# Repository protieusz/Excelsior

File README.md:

# Excelsior
Excelsior, 34 keys unisplit ortho with staggered pinkies &amp; 25mm trackball, optional RGB strip.

# Description
Excelsior is a heavily modified version of Endzone34 which has been blessed by takashicompany himself for the mod. [Endzone34](https://github.com/takashicompany/endzone34) was originally designed by takashicompany.

A List Of Mods Made To The Original PCB by [takashicompany](https://github.com/takashicompany/endzone34):

-PCB was created from scratch using the outline shape of Endzone34 using EasyEDA.

-A circular hole was created in the middle that can accomodate either a 25mm trackball powered by PMW3360 sensor.

-Base of the trackball holder with lens cut out is integrated into the top case with integrated 5mm switch plate. Top case sits flush with pcb.

-This PCB is capable of hot swap, Kailh.

-Full keyboard case was created to house the PCB.

-MCU area is now hidden and have an extrude of a [Starship logo](https://www.clipartmax.com/middle/m2i8Z5m2d3b1K9m2_star-trek-ship-icon-icon/)

-Excelsior is powered by [RP2040 Zero Raspberry Pi SuperMini Pico](https://www.aliexpress.com/item/1005007292787135.html?spm=a2g0o.order_list.order_list_main.136.6e251802pcq7qH) which you can get from AE and is soldered at the bottom of the pcb flush to the pcb.

-For diodes, I decided to try out the [BAV70](https://www.lcsc.com/product-detail/Switching-Diode_Jiangsu-Changjing-Electronics-Technology-Co-Ltd-BAV70_C68978.html) so that I solder less diodes since this pcb
is not sponsored. I would only need to solder on 17 diodes instead of 34.

-PCB has the option of RGB strip and the power 5v has the proper power level shifter component soldered on. Initially I was gonna do individual 34 RGBs but too much work and I don't use RGBs that often.

-QMK code is borrowed from aki27 bally and modified the matrix to fit my Excelsior. No suppport will be given since I just copy and paste.

-Keycaps I prefer high profile ones, MT3 or SA.

-Use M2 brass hot inserts 3.2mm diameter and 4mm length for the M2 screws to secure the case. I forgot how long is my M2 screws are but they should be greater than 10mm so estimated around 14.6mm. Play around with and buy multiple M2 lenght screws.

# Disclaimer
The trackball user experience might differ depending on the types of 3D printer that you use or if the printers were calibrated properly. It might be a hit and miss. The experience can also be adjust on the QMK side on the CPI settings. No
support will be given since the code was copy pasted from bally by aki27. As for the ball material and sizing plays a big role on the user experience. I personally prefer the BOM ball 25mm compared to the other different materials. Try it out and experiment it. As per usual print and use at your own risk. No support will be given. This design is MIT licensed so that means you can modify and do whatever you want with the design. If you do modify my design, please be kind to give me a shout out. PCB file is converted from EasyEDA so the convertion accuracy might not be good and KiCad DRC will scream but on EasyEDA DRC is fine. As the time of writing, the Excelsior is 100% working with no issues on my end.  Results might differ on your end.  A all in one Fusion file for the case that include the sketches is also included in this GitHub.  Thanks. 

# Full Production Pictures
TBA. Currently Sept 13, 2024, the PCBs are in transit from JLCPCB.
Sept 22, 2024, PCBs have arrived and build was a success!!!

# Renders

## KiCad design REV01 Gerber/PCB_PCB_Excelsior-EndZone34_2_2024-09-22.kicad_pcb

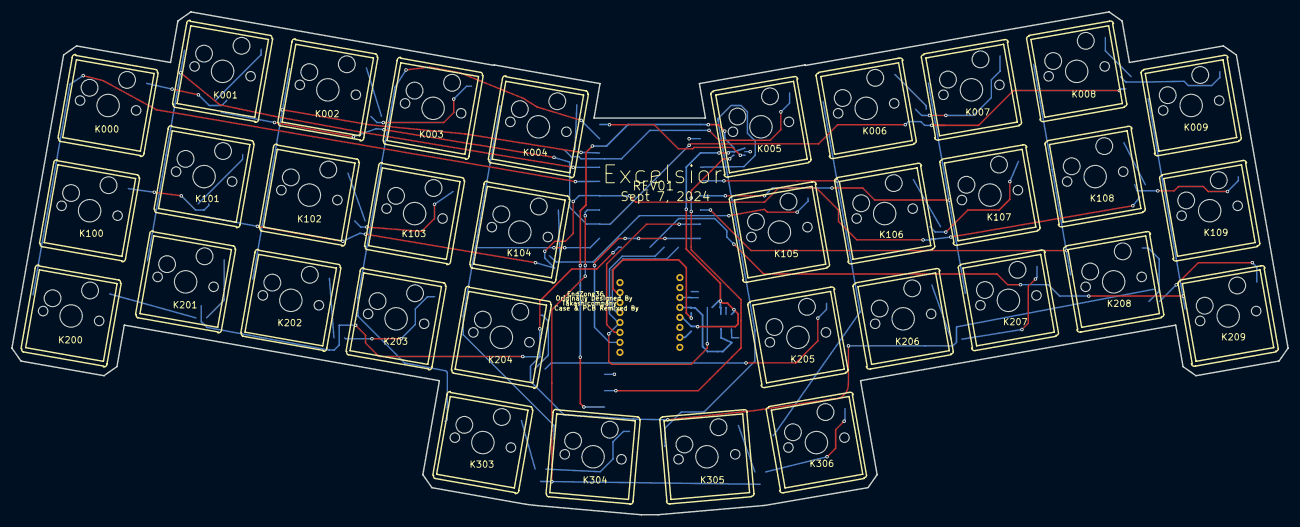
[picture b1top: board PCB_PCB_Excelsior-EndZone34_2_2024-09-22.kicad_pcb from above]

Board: 2 copper layers, 227.9 x 89.8 mm, 67 parts (0 on the bottom side), 62 nets.

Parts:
5V: NO; PIN 1-PIN
C17, C19, C20: 4.7uF; C0402
C18: 100nF; C0402
D000, D002, D004, D006, D008, D100, D102, D104, D106, D108, D200, D202, D204, D206, D208, D303, D305: BAV70-C68978; SOT-23-3_L3.0-W1.7-P0.95-LS2.9-BR
DIN: NO; PIN 1-PIN
GND: NO; PIN 1-PIN
K000, K001, K002, K003, K004, K005, K006, K007, K008, K009, K100, K101, K102, K103, K104, K105, K106, K107, K108, K109, K200, K201, K202, K203, K204, K205, K206, K207, K208, K209, K303, K304, K305, K306: Kailh MX Hotswap; KAILH MX HOTSWAP
R10, R12, R13: 10kΩ; R0402
R11: 39Ω; R0402
R14: 15kΩ; R0402
U2: RP2040-TINY; COMM-SMD_23P-P2.54-L23.5-W18.0_RP2040-TINY
U6: SN74LVC1T45QDCKRQ1; SC-70-6_L2.0-W1.3-P0.65-LS2.1-BR
U10: AP2127K-ADJTRG1; SOT-23-5_L3.0-W1.7-P0.95-LS2.8-BR
U11: PMW3360DM-T2QU; PMW3360DM-T2QU.PACK

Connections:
+2V: C20.2, R11.2, R14.2, U10.5, U11.4
+3V3: C19.2, R10.2, R12.2, U2.21, U6.1, U6.5, U10.1, U10.3, U11.5
+5V: 5V.1, U2.23, U6.6
C18_1: C17.1, C18.1, U11.3
COL0: K000.2, K100.2, K200.2, U2.5
COL1: K001.2, K101.2, K201.2, U2.4
COL2: K002.2, K102.2, K202.2, U2.3
COL3: K003.2, K103.2, K203.2, K303.2, U2.2
COL4: K004.2, K104.2, K204.2, K304.2, U2.9
COL5: K005.2, K105.2, K205.2, K305.2, U2.20
COL6: K006.2, K106.2, K206.2, K306.2, U2.19
COL7: K007.2, K107.2, K207.2, U2.18
COL8: K008.2, K108.2, K208.2, U2.17
COL9: K009.2, K109.2, K209.2, U2.12
CS: U2.14, U11.13
GND: C17.2, C18.2, C19.1, C20.1, GND.1, R13.1, U2.22, U6.2, U10.2, U11.8
K000_1: D000.2, K000.1
K001_1: D000.1, K001.1
K002_1: D002.2, K002.1
K003_1: D002.1, K003.1
K004_1: D004.2, K004.1
K005_1: D004.1, K005.1
K006_1: D006.2, K006.1
K007_1: D006.1, K007.1
K008_1: D008.2, K008.1
K009_1: D008.1, K009.1
K100_1: D100.2, K100.1
K101_1: D100.1, K101.1
K102_1: D102.2, K102.1
K103_1: D102.1, K103.1
K104_1: D104.2, K104.1
K105_1: D104.1, K105.1
K106_1: D106.2, K106.1
K107_1: D106.1, K107.1
K108_1: D108.2, K108.1
K109_1: D108.1, K109.1
K200_1: D200.2, K200.1
K201_1: D200.1, K201.1
K202_1: D202.2, K202.1
K203_1: D202.1, K203.1
K204_1: D204.2, K204.1
K205_1: D204.1, K205.1
K206_1: D206.2, K206.1
K207_1: D206.1, K207.1
K208_1: D208.2, K208.1
K209_1: D208.1, K209.1
K303_1: D303.1, K303.1
K304_1: D303.2, K304.1
K305_1: D305.1, K305.1
K306_1: D305.2, K306.1
MISO: R12.1, U2.13, U11.12
MOSI: U2.16, U11.11
R10_1: R10.1, U11.7
R11_1: R11.1, U11.15
R14_1: R13.2, R14.1, U10.4
RGB: DIN.1, U6.4
RGBMCU: U2.1, U6.3
ROW0: D000.3, D002.3, D004.3, D006.3, D008.3, U2.8
ROW1: D100.3, D102.3, D104.3, D106.3, D108.3, U2.6
ROW2: D200.3, D202.3, D204.3, D206.3, D208.3, U2.10
ROW3: D303.3, D305.3, U2.7
SCK: U2.15, U11.10

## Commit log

2024-09-13 CaseFiles in Fusion360
2024-09-22 EasyEDA json & KiCad PCB files
2024-09-22 QMK source code
2024-09-22 QMK firmware
